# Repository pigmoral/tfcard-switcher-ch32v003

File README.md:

TF-Card-Switcher-CH32V003

---

This project basically references [AvaotaHyperCard](https://github.com/AvaotaSBC/AvaotaHyperCard)

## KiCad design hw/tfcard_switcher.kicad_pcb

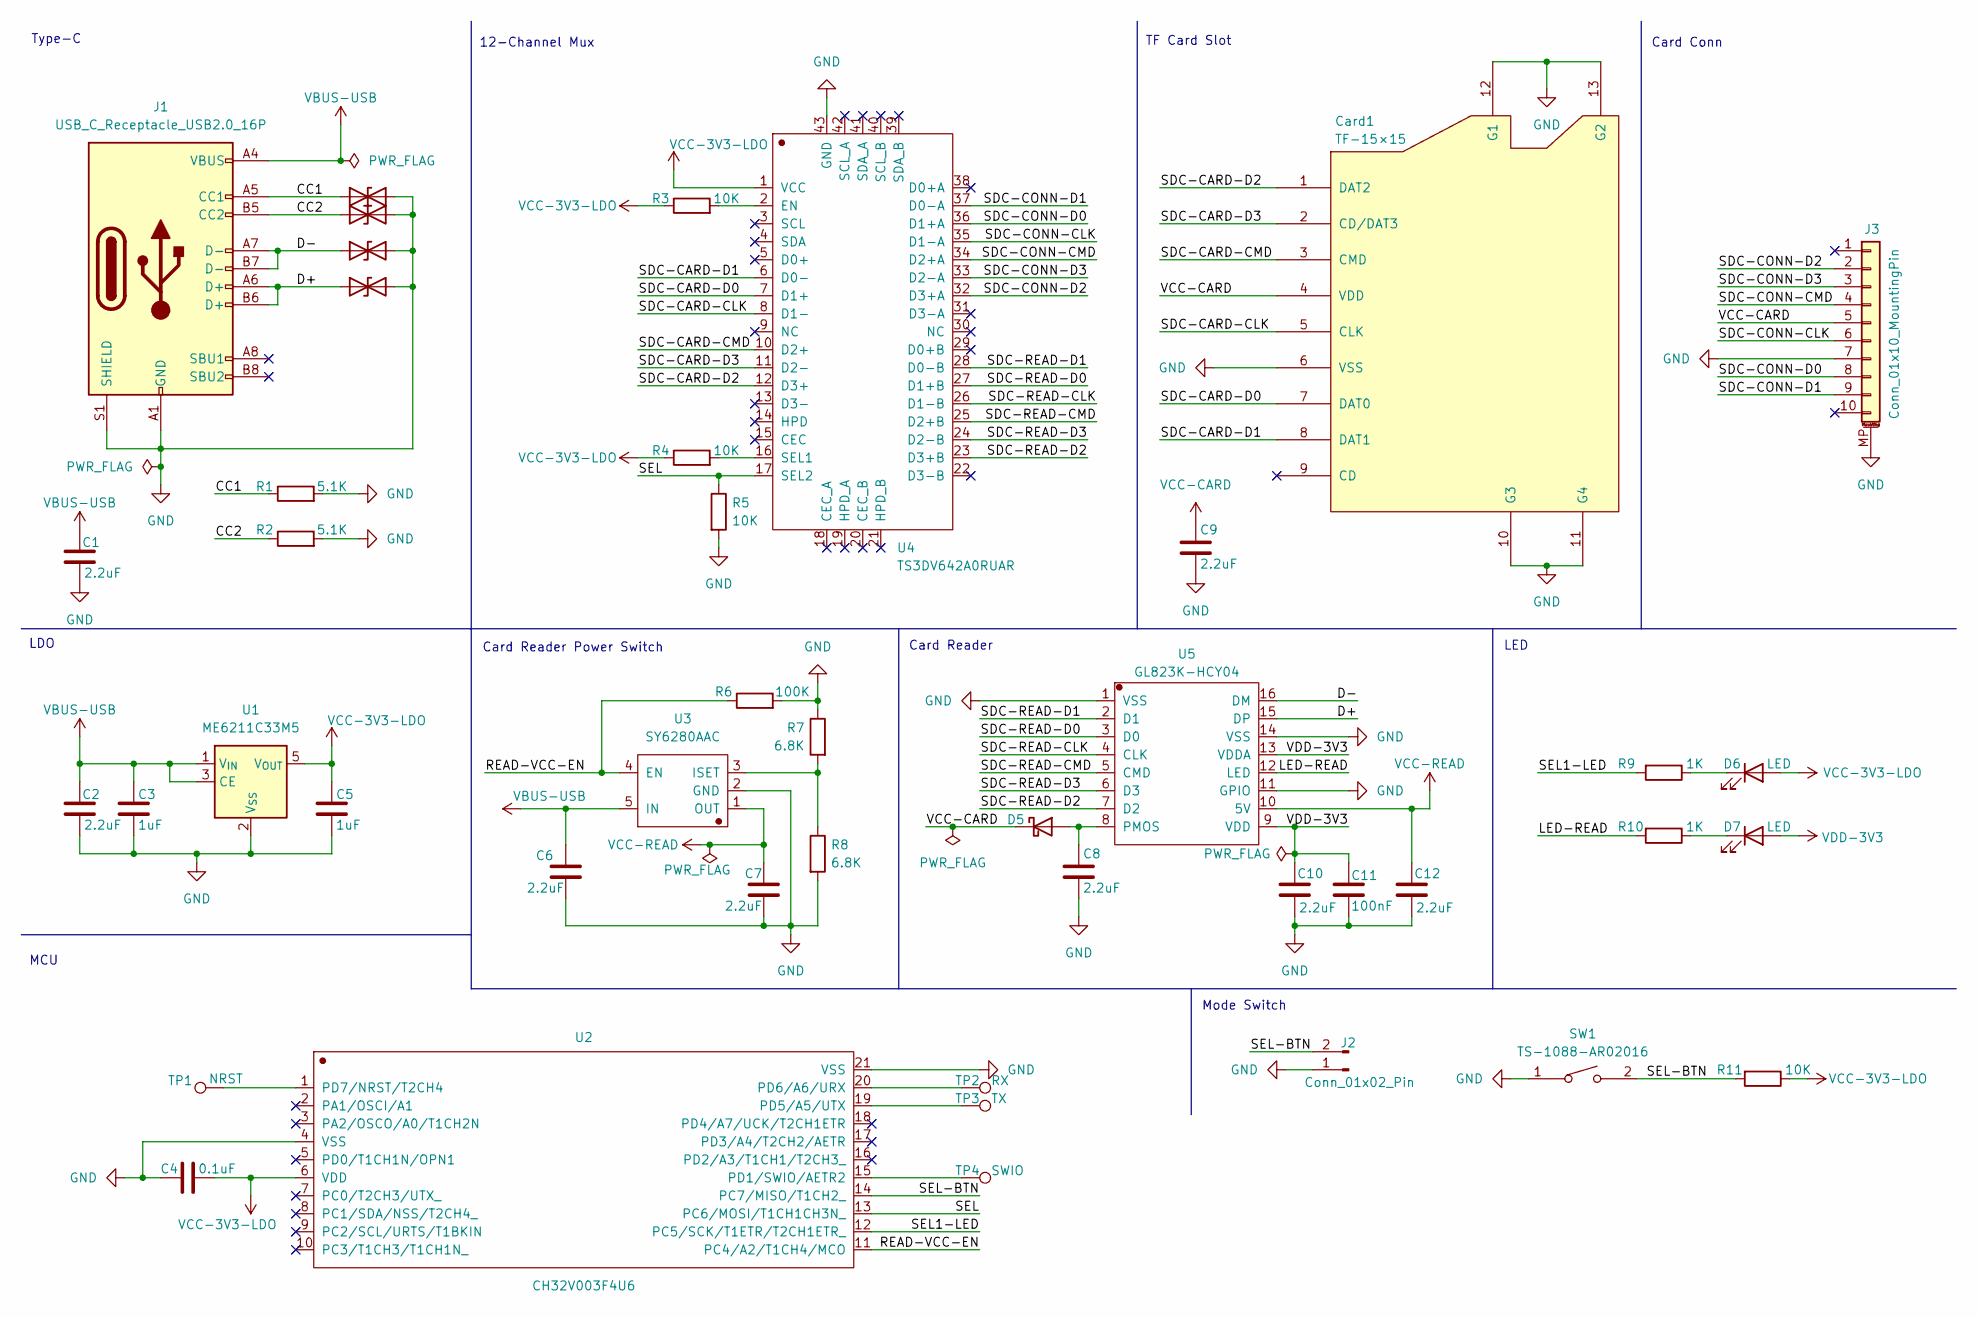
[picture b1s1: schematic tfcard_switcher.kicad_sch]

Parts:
C1, C2, C6, C7, C8, C9, C10, C12: 2.2uF; C_0603_1608Metric; Voltage 1kV; Tolerance 100%
C3, C5: 1uF; C_0603_1608Metric; Voltage 1kV; Tolerance 100%
C4: 0.1uF; C_0603_1608Metric; Voltage 1kV; Tolerance 100%
C11: 100nF; C_0603_1608Metric; Voltage 1kV; Tolerance 100%
Card1: TF-15×15; TF-SMD_TF-15-15
D1, D2, D3, D4: PESD0603-240; D_0603_1608Metric
D5: D_Schottky; D_SOD-523
D6, D7: LED; LED_0603_1608Metric
J1: USB_C_Receptacle_USB2.0_16P; USB_C_Receptacle_GCT_USB4110
J2: Conn_01x02_Pin; PinSocket_1x02_P2.54mm_Vertical
J3: Conn_01x10_MountingPin; TE_1-84952-0_1x10-1MP_P1.0mm_Horizontal
R1, R2: 5.1K; R_0603_1608Metric
R3, R4, R5, R11: 10K; R_0603_1608Metric
R6: 100K; R_0603_1608Metric
R7, R8: 6.8K; R_0603_1608Metric
R9, R10: 1K; R_0603_1608Metric
SW1: TS-1088-AR02016; SW-SMD_L3.9-W3.0-P4.45
TP1: NRST; TestPoint_Pad_D2.0mm
TP2: RX; TestPoint_Pad_D2.0mm
TP3: TX; TestPoint_Pad_D2.0mm
TP4: SWIO; TestPoint_Pad_D2.0mm
U1: ME6211C33M5; SOT-23-5
U2: CH32V003F4U6; QFN-20_L3.0-W3.0-P0.40-TL-EP1.7
U3: SY6280AAC; SOT-23-5_L3.0-W1.7-P0.95-LS2.8-BL
U4: TS3DV642A0RUAR; WFQFN-42_L9.0-W3.5-P0.50-BL-EP
U5: GL823K-HCY04; SSOP-16_L4.9-W3.9-P0.64-LS6.0-BL

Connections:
/CC1: D1.1 (A1), J1.A5 (CC1), R1.1
/CC2: D2.1 (A1), J1.B5 (CC2), R2.1
/D+: D4.1 (A1), J1.A6 (D+), J1.B6 (D+), U5.15 (DP)
/D-: D3.1 (A1), J1.A7 (D-), J1.B7 (D-), U5.16 (DM)
/LED-READ: R10.2, U5.12 (LED)
/READ-VCC-EN: R6.1, U2.11 (PC4/A2/T1CH4/MCO), U3.4 (EN)
/SDC-CARD-CLK: Card1.5 (CLK), U4.8 (D1-)
/SDC-CARD-CMD: Card1.3 (CMD), U4.10 (D2+)
/SDC-CARD-D0: Card1.7 (DAT0), U4.7 (D1+)
/SDC-CARD-D1: Card1.8 (DAT1), U4.6 (D0-)
/SDC-CARD-D2: Card1.1 (DAT2), U4.12 (D3+)
/SDC-CARD-D3: Card1.2 (CD/DAT3), U4.11 (D2-)
/SDC-CONN-CLK: J3.6, U4.35 (D1-A)
/SDC-CONN-CMD: J3.4, U4.34 (D2+A)
/SDC-CONN-D0: J3.8, U4.36 (D1+A)
/SDC-CONN-D1: J3.9, U4.37 (D0-A)
/SDC-CONN-D2: J3.2, U4.32 (D3+A)
/SDC-CONN-D3: J3.3, U4.33 (D2-A)
/SDC-READ-CLK: U4.26 (D1-B), U5.4 (CLK)
/SDC-READ-CMD: U4.25 (D2+B), U5.5 (CMD)
/SDC-READ-D0: U4.27 (D1+B), U5.3 (D0)
/SDC-READ-D1: U4.28 (D0-B), U5.2 (D1)
/SDC-READ-D2: U4.23 (D3+B), U5.7 (D2)
/SDC-READ-D3: U4.24 (D2-B), U5.6 (D3)
/SEL: R5.1, U2.13 (PC6/MOSI/T1CH1CH3N_), U4.17 (SEL2)
/SEL1-LED: R9.2, U2.12 (PC5/SCK/T1ETR/T2CH1ETR_)
/SEL-BTN: J2.2, R11.2, SW1.2, U2.14 (PC7/MISO/T1CH2_)
GND: C1.2, C2.2, C3.2, C4.1, C5.2, C6.2, C7.2, C8.2, C9.2, C10.2, C11.2, C12.2, Card1.6 (VSS), Card1.10 (G3), Card1.11 (G4), Card1.12 (G1), Card1.13 (G2), D1.2 (A2), D2.2 (A2), D3.2 (A2), D4.2 (A2), J1.A1 (GND), J1.A12 (GND), J1.B1 (GND), J1.B12 (GND), J1.S1 (SHIELD), J2.1, J3.7, J3.MP (MountPin), R1.2, R2.2, R5.2, R6.2, R7.1, R8.2, SW1.1, U1.2 (V_{SS}), U2.4 (VSS), U2.21 (VSS), U3.2 (GND), U4.43 (GND), U5.1 (VSS), U5.11 (GPIO), U5.14 (VSS)
unnamed: C8.1, D5.2 (A), U5.8 (PMOS)
unnamed: D6.1 (K), R9.1
unnamed: D7.1 (K), R10.1
unnamed: TP4.1, U2.15 (PD1/SWIO/AETR2)
unnamed: TP3.1, U2.19 (PD5/A5/UTX)
unnamed: TP2.1, U2.20 (PD6/A6/URX)
unnamed: TP1.1, U2.1 (PD7/NRST/T2CH4)
unnamed: R7.2, R8.1, U3.3 (ISET)
unnamed: R3.2, U4.2 (EN)
unnamed: R4.2, U4.16 (SEL1)
VBUS-USB: C1.1, C2.1, C3.1, C6.1, J1.A4 (VBUS), J1.A9 (VBUS), J1.B4 (VBUS), J1.B9 (VBUS), U1.1 (V_{IN}), U1.3 (CE), U3.5 (IN)
VCC-3V3-LDO: C4.2, C5.1, D6.2 (A), R3.1, R4.1, R11.1, U1.5 (V_{OUT}), U2.6 (VDD), U4.1 (VCC)
VCC-CARD: C9.1, Card1.4 (VDD), D5.1 (K), J3.5
VCC-READ: C7.1, C12.1, U3.1 (OUT), U5.10 (5V)
VDD-3V3: C10.1, C11.1, D7.2 (A), U5.9 (VDD), U5.13 (VDDA)

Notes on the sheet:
TF Card Slot
LDO
12-Channel Mux
LED
Type-C
Mode Switch
Card Reader Power Switch
Card Reader
MCU
Card Conn

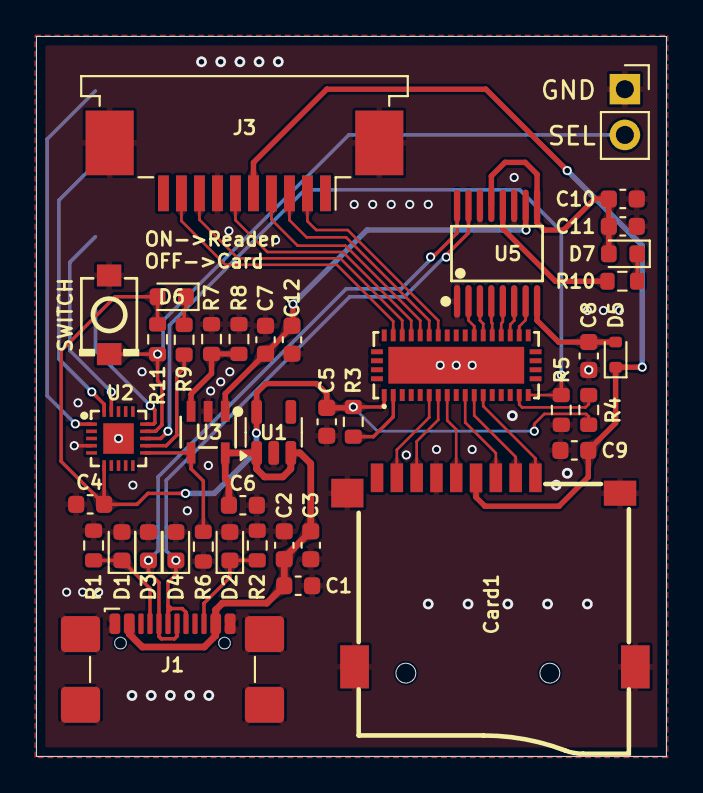
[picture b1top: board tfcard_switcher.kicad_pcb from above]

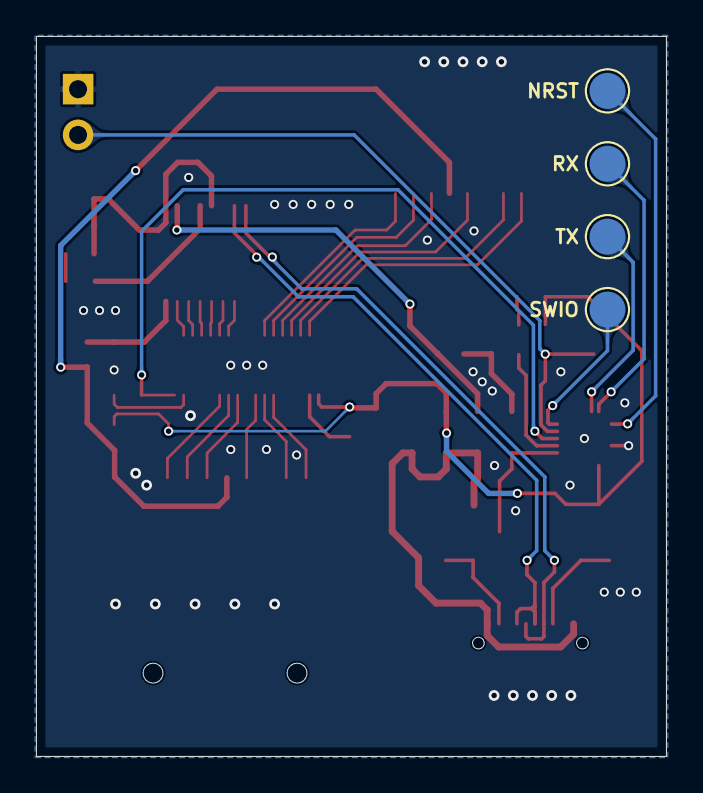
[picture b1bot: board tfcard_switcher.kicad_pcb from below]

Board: 2 copper layers, 35.0 x 40.0 mm, 44 parts (4 on the bottom side), 43 nets.

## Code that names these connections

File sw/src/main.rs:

#![no_std]
#![no_main]
#![feature(type_alias_impl_trait)]
#![feature(impl_trait_in_assoc_type)]

use Level::{High, Low};
use ch32_hal as hal;
use embassy_executor::Spawner;
use hal::delay::Delay;
use hal::exti::ExtiInput;
use hal::gpio::{Level, Output, Pull};

#[embassy_executor::main(entry = "qingke_rt::entry")]
async fn main(_spawner: Spawner) -> ! {
    let mut config = hal::Config::default();
    config.rcc = hal::rcc::Config::SYSCLK_FREQ_48MHZ_HSI;
    let p = hal::init(config);

    let mut read_vcc_en = Output::new(p.PC4, Low, Default::default());
    let mut sel_led = Output::new(p.PC5, High, Default::default());
    let mut mux_sel = Output::new(p.PC6, Low, Default::default());
    let sel_btn = ExtiInput::new(p.PC7, p.EXTI7, Pull::None);

    loop {
        if sel_btn.is_high() {
            read_vcc_en.set_level(Low);
            sel_led.set_level(High);
            mux_sel.set_level(Low);
        } else {
            read_vcc_en.set_level(High);
            sel_led.set_level(Low);
            mux_sel.set_level(High);
        }

        Delay.delay_ms(100);
    }
}

#[panic_handler]
fn panic(info: &core::panic::PanicInfo) -> ! {
    let _ = hal::println!("\n\n\n{}", info);

    loop {}
}

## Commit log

2024-12-17 Initial commit, add hw and sw
2024-12-17 Add LICENSE and README
2025-06-10 sw: Add delay to reduce jitter
2025-06-10 sw: Add README
2025-06-10 sw: Add signal flip branch
2025-06-13 sw: Update README.md
